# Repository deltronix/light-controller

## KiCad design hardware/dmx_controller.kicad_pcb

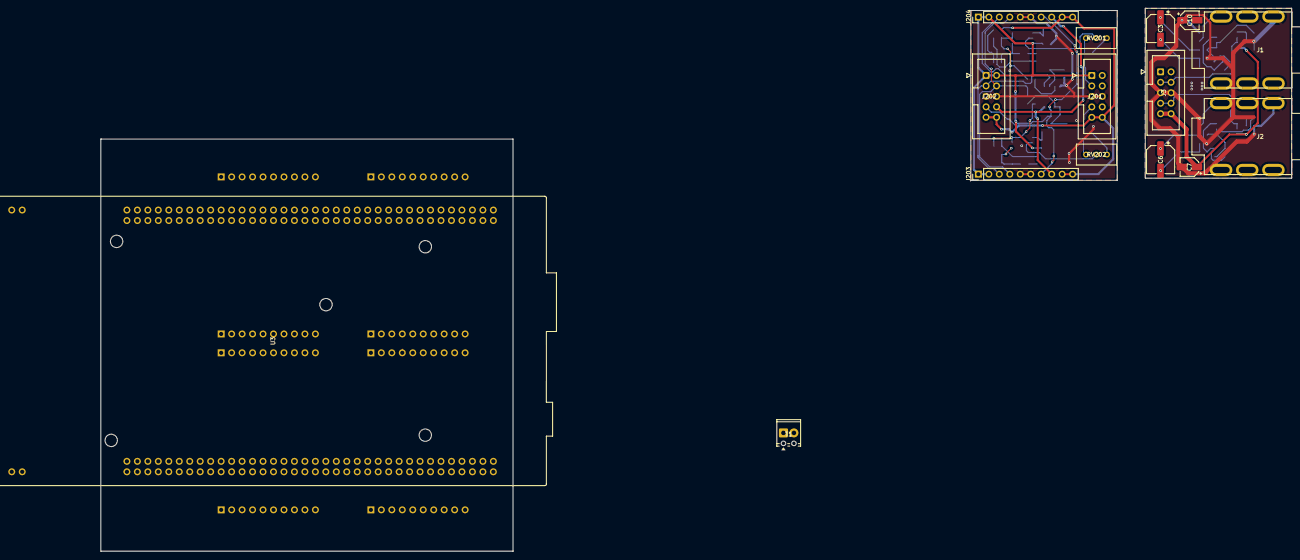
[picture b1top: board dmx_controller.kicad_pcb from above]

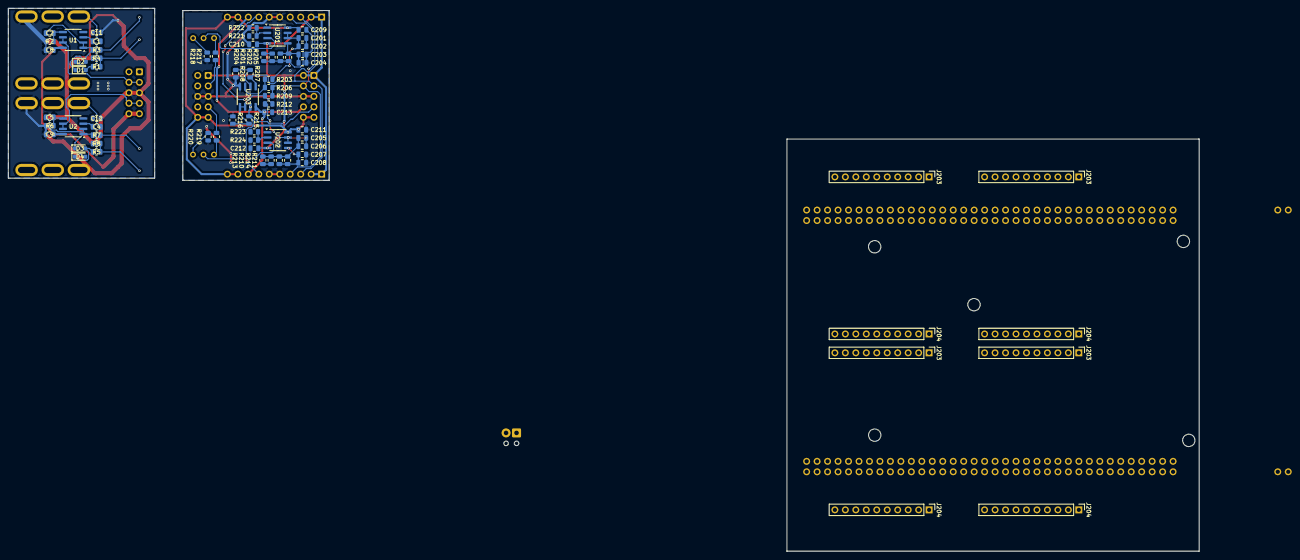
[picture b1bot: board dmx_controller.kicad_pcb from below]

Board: 2 copper layers, 288.9 x 131.7 mm, 85 parts (70 on the bottom side), 43 nets.

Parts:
C1, C4: 4n7; C_0805_2012Metric
C2, C5: 220n; C_0805_2012Metric
C3, C6: 33u; CP_Elec_6.3x5.8
C7, C10: 1u; CP_Elec_4x5.4
C8, C9, C11, C12, C209, C210, C211, C212, C213: 100n; C_0805_2012Metric
C201, C202, C205, C206: 5n6; C_0805_2012Metric
C203, C204, C207, C208: 3n3; C_0805_2012Metric
D1, D2, D3, D4: D; D_SOD-323_HandSoldering
J1, J2: AudioJack2; Cheap Jack
J3, J201, J202: Conn_02x05_Odd_Even; IDC-Header_2x05_P2.54mm_Vertical
J203, J203#2, J203#3, J203#4, J203#5, J204, J204#2, J204#3, J204#4, J204#5: Conn_01x10; PinHeader_1x10_P2.54mm_Vertical
R1, R4, R5, R8: 1M; R_0805_2012Metric
R2, R6: 22k; R_0805_2012Metric
R3, R7: 3k9; R_0805_2012Metric
R201, R204, R210, R213: 2k61; R_0805_2012Metric
R202, R205, R211, R214: 7k15; R_0805_2012Metric
R203, R206, R207, R208, R209, R212, R215, R216: 10k; R_0805_2012Metric
R217, R218, R219, R220, R221, R222, R223, R224: 0R; R_0805_2012Metric
RV201, RV202: R_Potentiometer; Potentiometer_Bourns_3296W_Vertical
T1: Screw_Terminal_01x02; TerminalBlock_Phoenix_MPT-0,5-2-2.54_1x02_P2.54mm_Horizontal
U1, U2, U201, U202: TL072; SOIC-8_3.9x4.9mm_P1.27mm
U3: NUCLEO144-H743ZI; ST_Morpho_Connector_144_STLink_MountingHoles
U203: MCP6002-xSN; SOIC-8_3.9x4.9mm_P1.27mm

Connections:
+3.3V: C213.2, J202.8, J203.8, J203#2.8, J203#3.8, J203#4.8, J203#5.8, J204.8, J204#2.8, J204#3.8, J204#4.8, J204#5.8, U203.8 (V+)
+3V3: U3.16 (+3V3), U3.79 (AVDD)
+12V: C7.1, C8.2, C9.2, C209.2, C211.2, J3.9, J3.10, J201.9, J201.10, J202.9, J202.10, J203.9, J203.10, J203#2.9, J203#2.10, J203#3.9, J203#3.10, J203#4.9, J203#4.10, J203#5.9, J203#5.10, J204.9, J204.10, J204#2.9, J204#2.10, J204#3.9, J204#3.10, J204#4.9, J204#4.10, J204#5.9, J204#5.10, T1.2, U1.8 (V+), U2.8 (V+), U3.24 (VIN), U201.8 (V+), U202.8 (V+)
-12V: C10.2, C11.1, C12.1, C210.1, C212.1, J3.1, J3.2, J201.1, J201.2, J202.1, J202.2, J203.1, J203.2, J203#2.1, J203#2.2, J203#3.1, J203#3.2, J203#4.1, J203#4.2, J203#5.1, J203#5.2, J204.1, J204.2, J204#2.1, J204#2.2, J204#3.1, J204#3.2, J204#4.1, J204#4.2, J204#5.1, J204#5.2, U1.4 (V-), U2.4 (V-), U201.4 (V-), U202.4 (V-)
/analog_conditioning/V_REF_1_65V: J202.4, J203.4, J203#2.4, J203#3.4, J203#4.4, J203#5.4, J204.4, J204#2.4, J204#3.4, J204#4.4, J204#5.4, R206.2, R209.1
/analog_conditioning/analog_in_1: J201.3, R217.1
/analog_conditioning/analog_in_2: J201.7, R219.1
/analog_conditioning/analog_out_1: J202.3, J203.3, J203#2.3, J203#3.3, J203#4.3, J203#5.3, J204.3, J204#2.3, J204#3.3, J204#4.3, J204#5.3, R207.1, U203.1
/analog_conditioning/analog_out_2: J202.7, J203.7, J203#2.7, J203#3.7, J203#4.7, J203#5.7, J204.7, J204#2.7, J204#3.7, J204#4.7, J204#5.7, R215.1, U203.7
GND: C7.2, C8.1, C9.1, C10.1, C11.2, C12.2, C203.2, C204.2, C207.2, C208.2, C209.1, C210.2, C211.1, C212.2, C213.1, J1.S, J2.S, J3.5, J3.6, J201.5, J201.6, J202.5, J202.6, J203.5, J203.6, J203#2.5, J203#2.6, J203#3.5, J203#3.6, J203#4.5, J203#4.6, J203#5.5, J203#5.6, J204.5, J204.6, J204#2.5, J204#2.6, J204#3.5, J204#3.6, J204#4.5, J204#4.6, J204#5.5, J204#5.6, R2.1, R4.1, R6.1, R8.1, R208.2, R216.2, R218.2, R220.2, R222.2, R224.2, T1.1, U3.8 (GND), U3.19 (GND), U3.20 (GND), U3.22 (GND), U3.49 (GND), U3.60 (GND), U3.71 (GND), U3.72 (GND), U3.81 (GND), U3.92 (GND), U3.111 (GND), U3.126 (GND), U3.135 (GND), U3.143 (GND), U3.144 (GND), U203.4 (V-)
unnamed: C1.1, J1.T
unnamed: C3.1, R3.1
unnamed: C3.2, R1.2, R4.2
unnamed: C4.1, J2.T
unnamed: C6.1, R7.1
unnamed: C6.2, R5.2, R8.2
unnamed: C201.1, C202.1, R201.2, R202.1, R204.2, R205.1
unnamed: C205.1, C206.1, R210.2, R211.1, R213.2, R214.1
unnamed: C1.2, D1.2 (A), D2.1 (K), R1.1, U1.3 (+)
unnamed: C2.1, D1.1 (K), D2.2 (A), R3.2, U1.1, U1.2 (-)
unnamed: C4.2, D3.2 (A), D4.1 (K), R5.1, U2.3 (+)
unnamed: C5.1, D3.1 (K), D4.2 (A), R7.2, U2.1, U2.2 (-)
unnamed: J3.3, J3.4, U1.6 (-), U1.7
unnamed: J3.7, J3.8, U2.6 (-), U2.7
unnamed: R201.1, R204.1, R221.2, U201.1
unnamed: R210.1, R213.1, R223.2, U202.1
unnamed: R217.2, RV201.1
unnamed: R218.1, RV201.3
unnamed: R219.2, RV202.1
unnamed: R220.1, RV202.3
unnamed: C2.2, R2.2, U1.5 (+)
unnamed: C5.2, R6.2, U2.5 (+)
unnamed: RV201.2, U201.3 (+)
unnamed: R221.1, R222.1, U201.2 (-)
unnamed: C203.1, C204.1, R202.2, R205.2, U201.5 (+)
unnamed: C201.2, C202.2, R203.1, U201.6 (-), U201.7
unnamed: RV202.2, U202.3 (+)
unnamed: R223.1, R224.1, U202.2 (-)
unnamed: C207.1, C208.1, R211.2, R214.2, U202.5 (+)
unnamed: C205.2, C206.2, R212.1, U202.6 (-), U202.7
unnamed: R203.2, R206.1, U203.3 (+)
unnamed: R207.2, R208.1, U203.2 (-)
unnamed: R209.2, R212.2, R215.2, R216.1, U203.5 (+), U203.6 (-)

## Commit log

2025-03-07 init
2025-03-08 overrun at high FS
2025-03-09 works up to at least 24kHz
2025-03-09 working led_controller
2025-03-10 working example
2025-03-11 cleanup dasp code from main
2025-03-11 edited DEVLOG
2025-03-11 enabled host compilation for testing
2025-03-26 cleanup dead code
2025-03-26 switched dependencies to embassy git
2025-03-26 rename and cleanup
2025-03-26 fucked up host testing
2025-03-26 fixed host testing
2025-03-26 working external board init
2025-03-26 split out env
2025-04-01 trig process was in the wrong spot
2025-04-01 changed SPI1 pinout
2025-04-01 added prototype p9813 code for testing
2025-04-02 hardware
2025-04-07 changed p9813 spi settings
2025-04-07 multiple led driver modules
2025-05-25 hardware update
2025-05-25 spi from embassy
2025-05-25 lib for cross platform testing
2025-06-06 analog conditioning and preamp board sent for prototype manufacture
2025-11-19 change?
